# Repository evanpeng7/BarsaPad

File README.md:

# BarsaPad
This is my Hackpad submission repository for Hackclub x AMD Blueprint.

# Features
* Sandwich mount design
* EC11 Rotary Encoder
* 3 Keys
* 0.91" OLED display

# CAD 
The plate and bottom case will be screwed together by 4 M3 screws with use of heatset inserts positioned on the bottom case and clearance holes located in the corners of the plate. The models were designed in Fusion360.

# PCB
Schematic and PCB:

Designed with KiCad

# Firmware
I wrote the firmware using QMK Firmware.

# BOM
* 1x Seeed XIAO RP2040
* 3x through-hole 1N4148 Diodes
* 3x MX-Style switches
* 1x EC11 Rotary encoders
* 1x 0.91 inch OLED display
* 3x white blank DSA keycaps
* 4x M3x16mm screws
* 4x M3x5mx4mm heatset inserts
* 1x Case (2 printed parts)

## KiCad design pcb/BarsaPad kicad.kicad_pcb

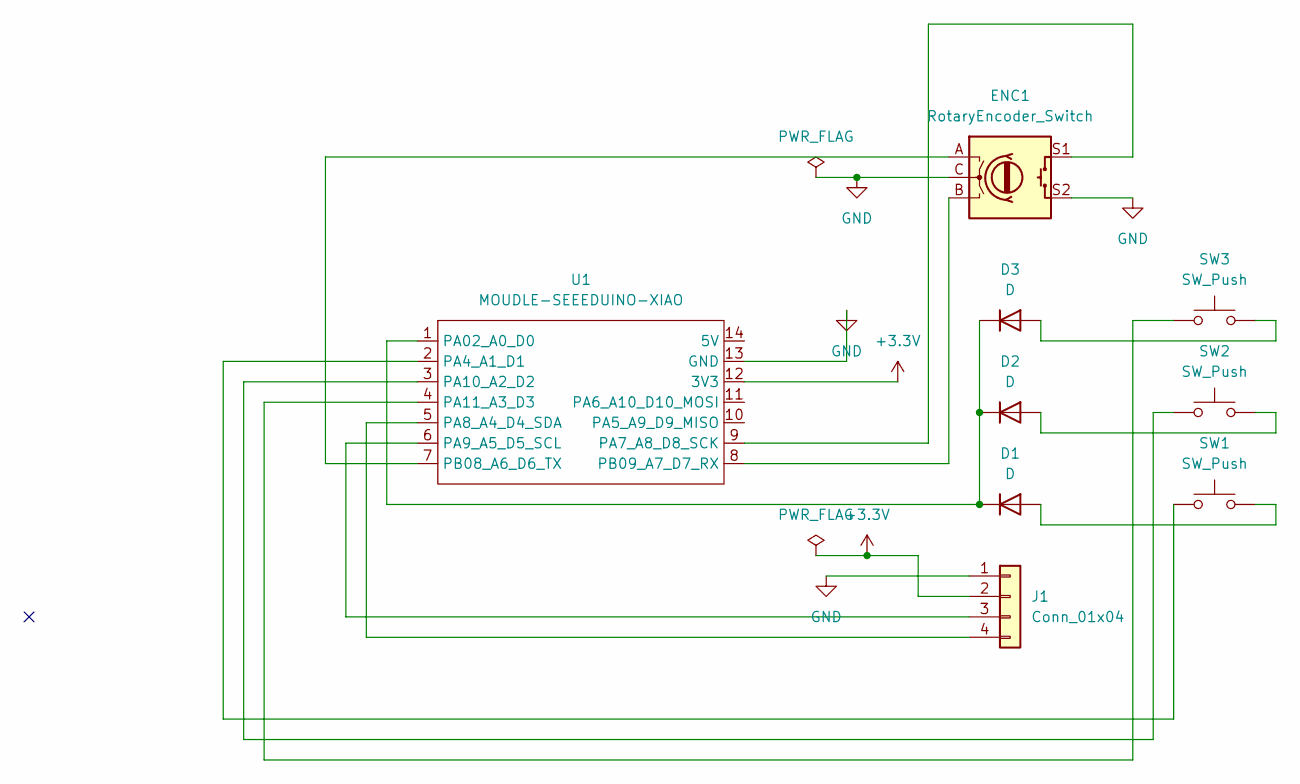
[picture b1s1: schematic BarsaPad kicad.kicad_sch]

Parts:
D1, D2, D3: D; D_DO-35_SOD27_P7.62mm_Horizontal
ENC1: RotaryEncoder_Switch; RotaryEncoder_Alps_EC11E-Switch_Vertical_H20mm
J1: Conn_01x04; PinHeader_1x04_P2.54mm_Vertical
SW1, SW2, SW3: SW_Push; SW_Cherry_MX_1.00u_PCB
U1: MOUDLE-SEEEDUINO-XIAO; XIAO-Generic-Hybrid-14P-2.54-21X17.8MM

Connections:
+3.3V: J1.2, U1.12 (3V3)
GND: ENC1.C, ENC1.S2, J1.1, U1.13 (GND)
unnamed: D1.2 (A), SW1.2
unnamed: D1.1 (K), D2.1 (K), D3.1 (K), U1.1 (PA02_A0_D0)
unnamed: D2.2 (A), SW2.2
unnamed: D3.2 (A), SW3.2
unnamed: J1.3, U1.6 (PA9_A5_D5_SCL)
unnamed: J1.4, U1.5 (PA8_A4_D4_SDA)
unnamed: SW1.1, U1.2 (PA4_A1_D1)
unnamed: ENC1.S1, U1.9 (PA7_A8_D8_SCK)
unnamed: SW2.1, U1.3 (PA10_A2_D2)
unnamed: SW3.1, U1.4 (PA11_A3_D3)
unnamed: ENC1.A, U1.7 (PB08_A6_D6_TX)
unnamed: ENC1.B, U1.8 (PB09_A7_D7_RX)

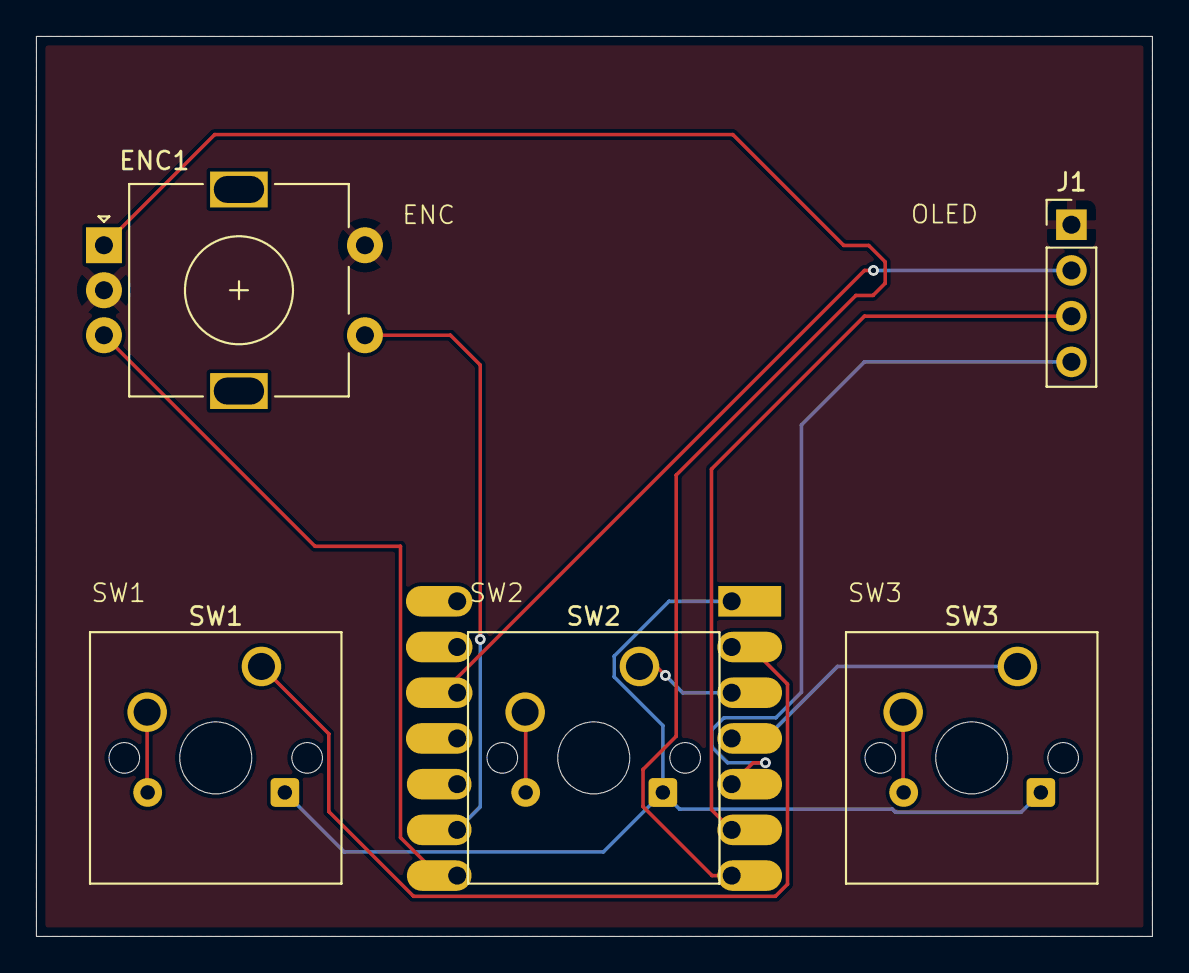
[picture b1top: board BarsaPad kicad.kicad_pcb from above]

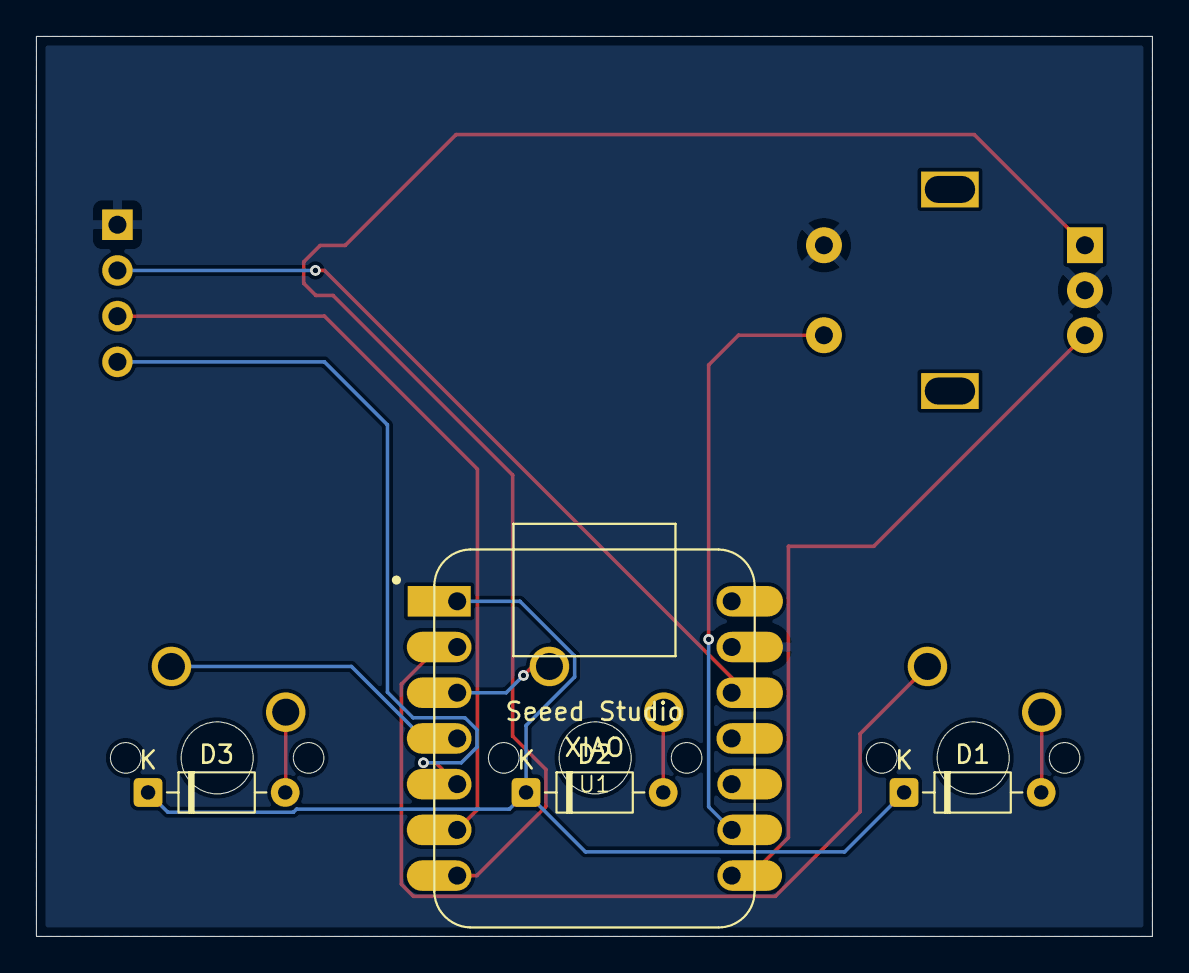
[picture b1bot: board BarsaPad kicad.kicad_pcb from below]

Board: 2 copper layers, 62.0 x 50.0 mm, 9 parts (4 on the bottom side), 14 nets.

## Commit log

2026-02-15 prod
2026-02-15 updated cad
